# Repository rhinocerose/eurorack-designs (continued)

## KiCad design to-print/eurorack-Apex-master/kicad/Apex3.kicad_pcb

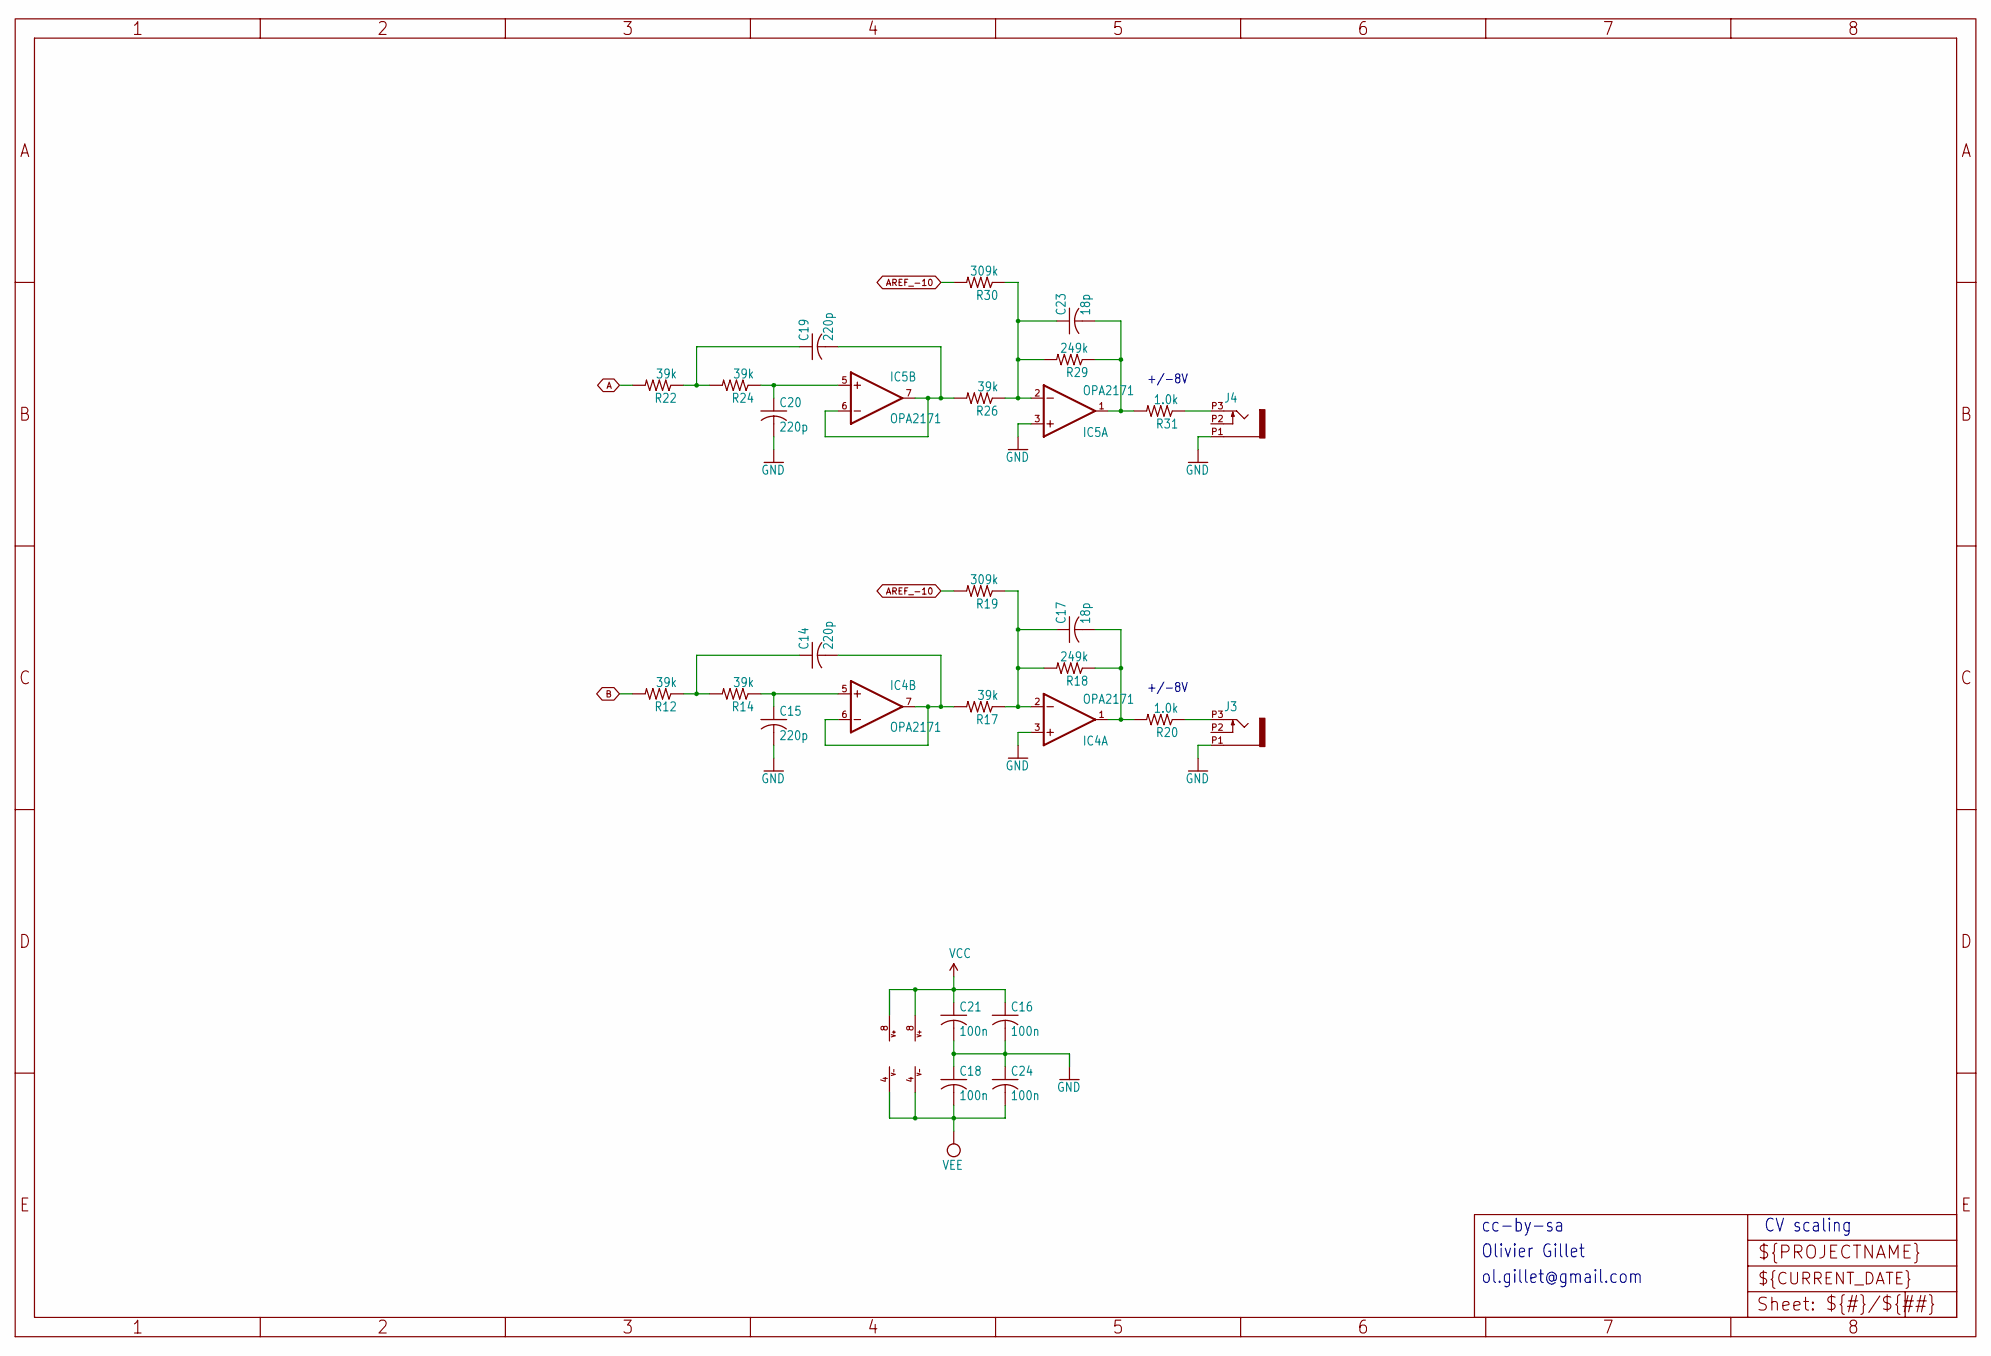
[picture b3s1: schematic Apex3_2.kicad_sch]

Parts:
C14, C15, C19, C20: 220p; C0603
C16, C18, C21, C24: 100n; C0603
C17, C23: 18p; C0603
IC4, IC5: OPA2171; SO08
J3, J4: OG-PJ301_PJ301_THONKICONN; OG-PJ301_WQP_PJ_301M6_NO_HOLE
R12, R14, R17, R22, R24, R26: 39k; R0603
R18, R29: 249k; R0603
R19, R30: 309k; R0603
R20, R31: 1.0k; R0603

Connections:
A: R22.2; also elsewhere on the board
AREF_-10: R19.2, R30.2; also elsewhere on the board
B: R12.2; also elsewhere on the board
BI_OUT: C17.2, IC4.1 (OUT), R18.1, R20.2
BI_OUT1: C23.2, IC5.1 (OUT), R29.1, R31.2
F_CV: C17.1, IC4.2 (-IN), R17.1, R18.2, R19.1
F_CV1: C23.1, IC5.2 (-IN), R26.1, R29.2, R30.1
GND: C15.2, C16.2, C18.1, C20.2, C21.2, C24.1, IC4.3 (+IN), IC5.3 (+IN), J3.P1 (1), J4.P1 (1); also elsewhere on the board
unnamed: C19.2, IC5.6 (-IN), IC5.7 (OUT), R26.2
unnamed: C20.1, IC5.5 (+IN), R24.1
unnamed: C19.1, R22.1, R24.2
unnamed: J3.P3 (3), R20.1
unnamed: J4.P3 (3), R31.1
unnamed: C14.2, IC4.6 (-IN), IC4.7 (OUT), R17.2
unnamed: C15.1, IC4.5 (+IN), R14.1
unnamed: C14.1, R12.1, R14.2
VCC: C16.1, C21.1, IC4.8 (V+), IC5.8 (V+); also elsewhere on the board
VEE: C18.2, C24.2, IC4.4 (V-), IC5.4 (V-); also elsewhere on the board

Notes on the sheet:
cc-by-sa
+/-8V
Olivier Gillet
CV scaling
ol.gillet@gmail.com

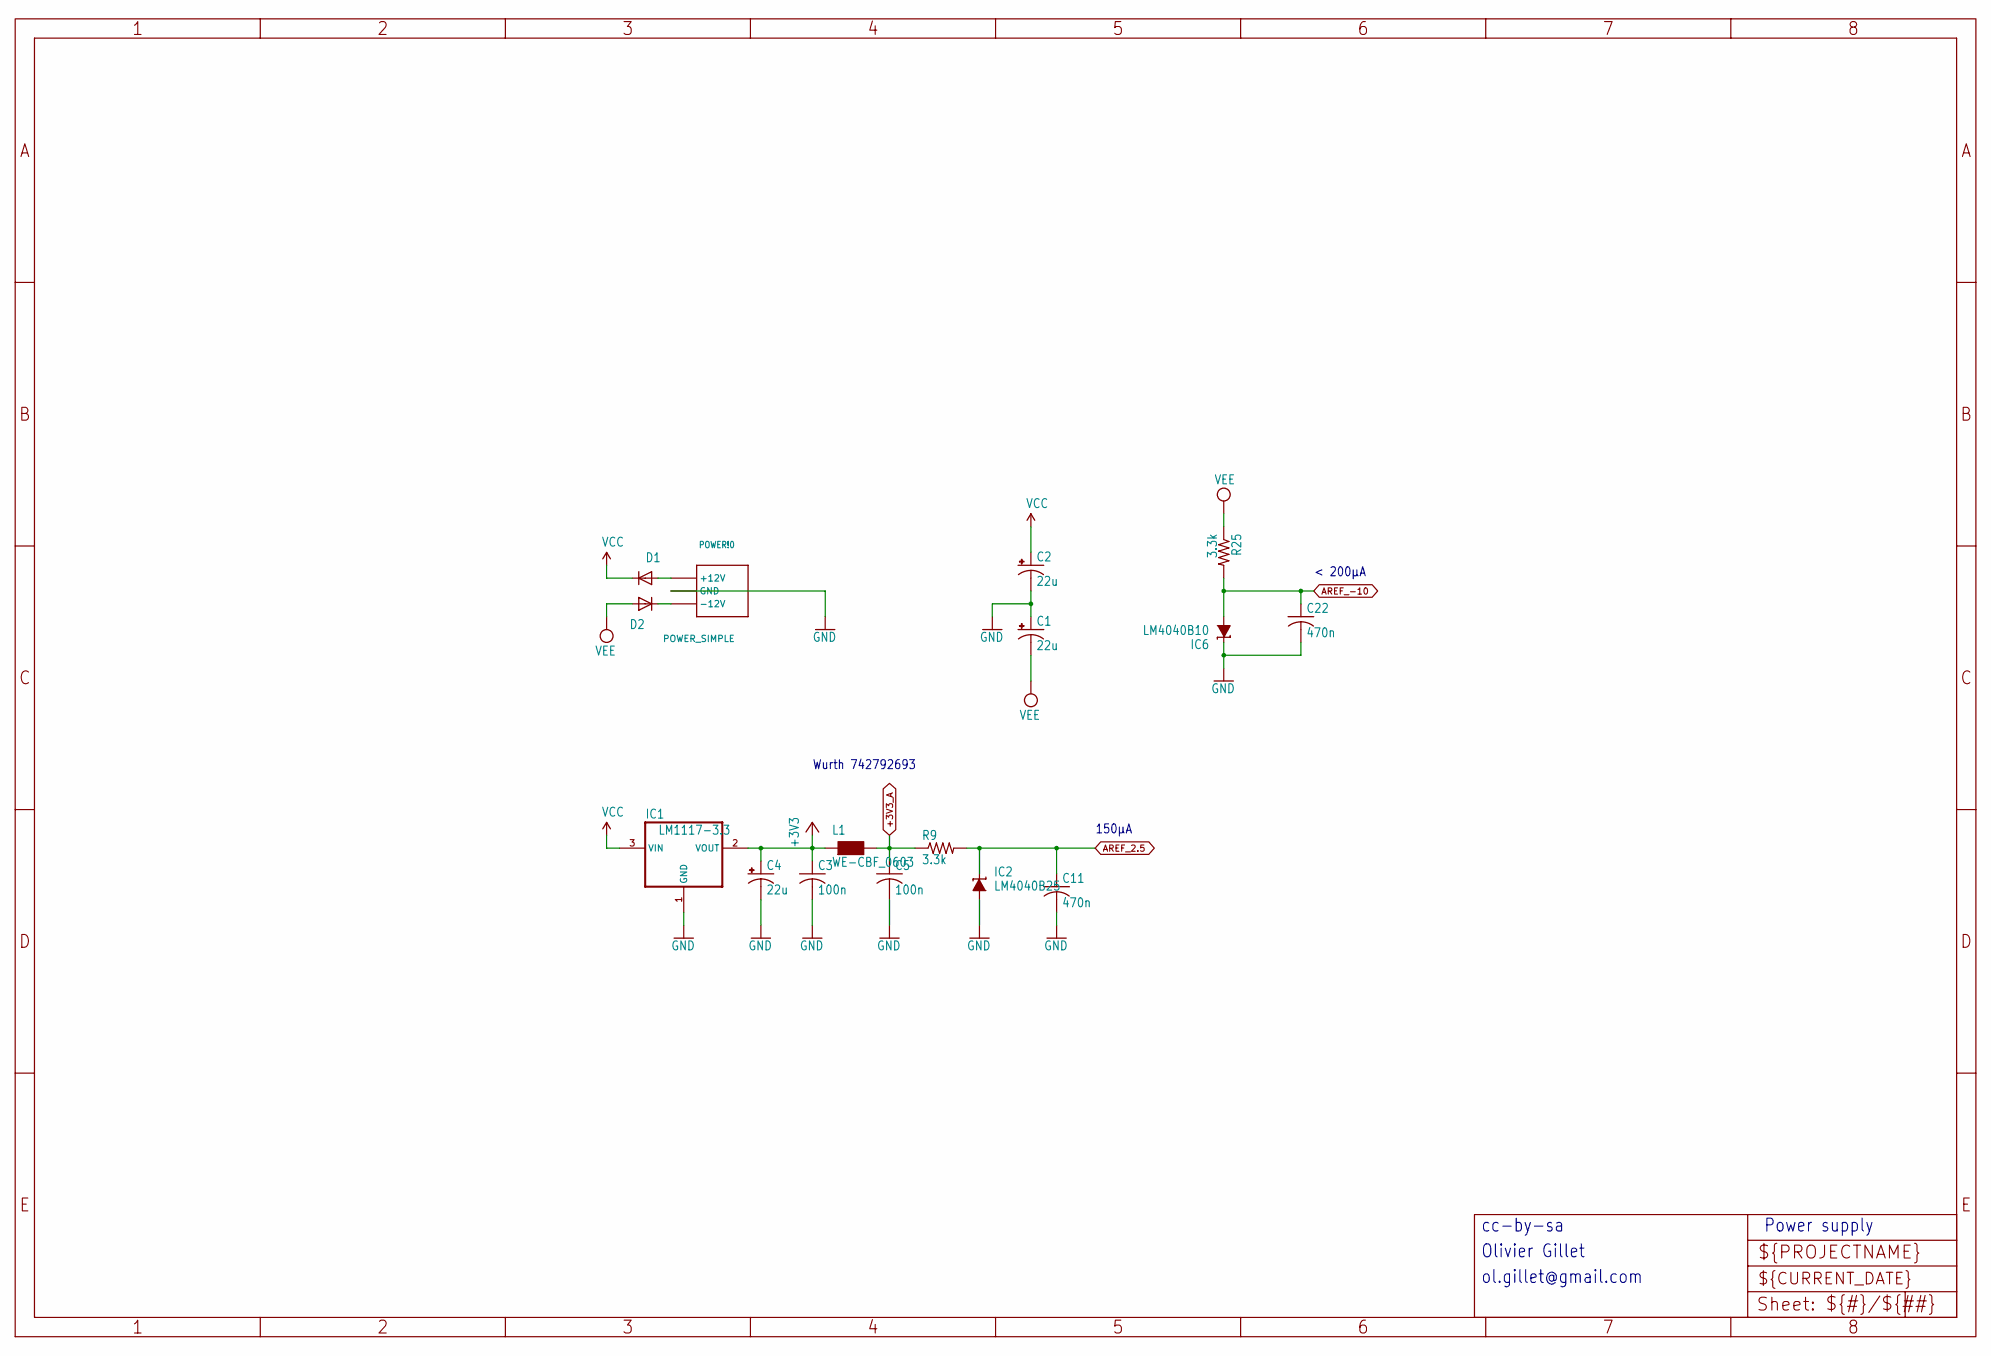
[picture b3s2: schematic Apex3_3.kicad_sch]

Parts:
C1, C2, C4: 22u; PANASONIC_C
C3, C5: 100n; C0603
C11, C22: 470n; C0603
D1, D2: 1N5819HW; SOD123
IC1: LM1117-3.3; SOT223
IC2: LM4040B25; DBZ_R-PDSO-G3
IC6: LM4040B10; DBZ_R-PDSO-G3
L1: WE-CBF_0603; 0603
POWER!0: POWER_SIMPLE; 2X05_SMT_HEADER
R9, R25: 3.3k; R0603

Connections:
+3V3: C3.1, C4.+, IC1.2 (VOUT), L1.1; also elsewhere on the board
+3V3_A: C5.1, L1.2, R9.1; also elsewhere on the board
AREF_2.5: C11.1, IC2.1 (C), R9.2; also elsewhere on the board
AREF_-10: C22.1, IC6.2 (A), R25.2; also elsewhere on the board
GND: C1.+, C2.-, C3.2, C4.-, C5.2, C11.2, C22.2, IC1.1 (GND), IC2.2 (A), IC6.1 (C), POWER!0.3 (GND), POWER!0.4 (GND), POWER!0.5 (GND), POWER!0.6 (GND), POWER!0.7 (GND), POWER!0.8 (GND); also elsewhere on the board
unnamed: D1.A, POWER!0.9 (+12V), POWER!0.10 (+12V)
unnamed: D2.C, POWER!0.1 (-12V), POWER!0.2 (-12V)
VCC: C2.+, D1.C, IC1.3 (VIN); also elsewhere on the board
VEE: C1.-, D2.A, R25.1; also elsewhere on the board

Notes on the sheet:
ol.gillet@gmail.com
Olivier Gillet
Wurth 742792693
150µA
Power supply
cc-by-sa
< 200µA

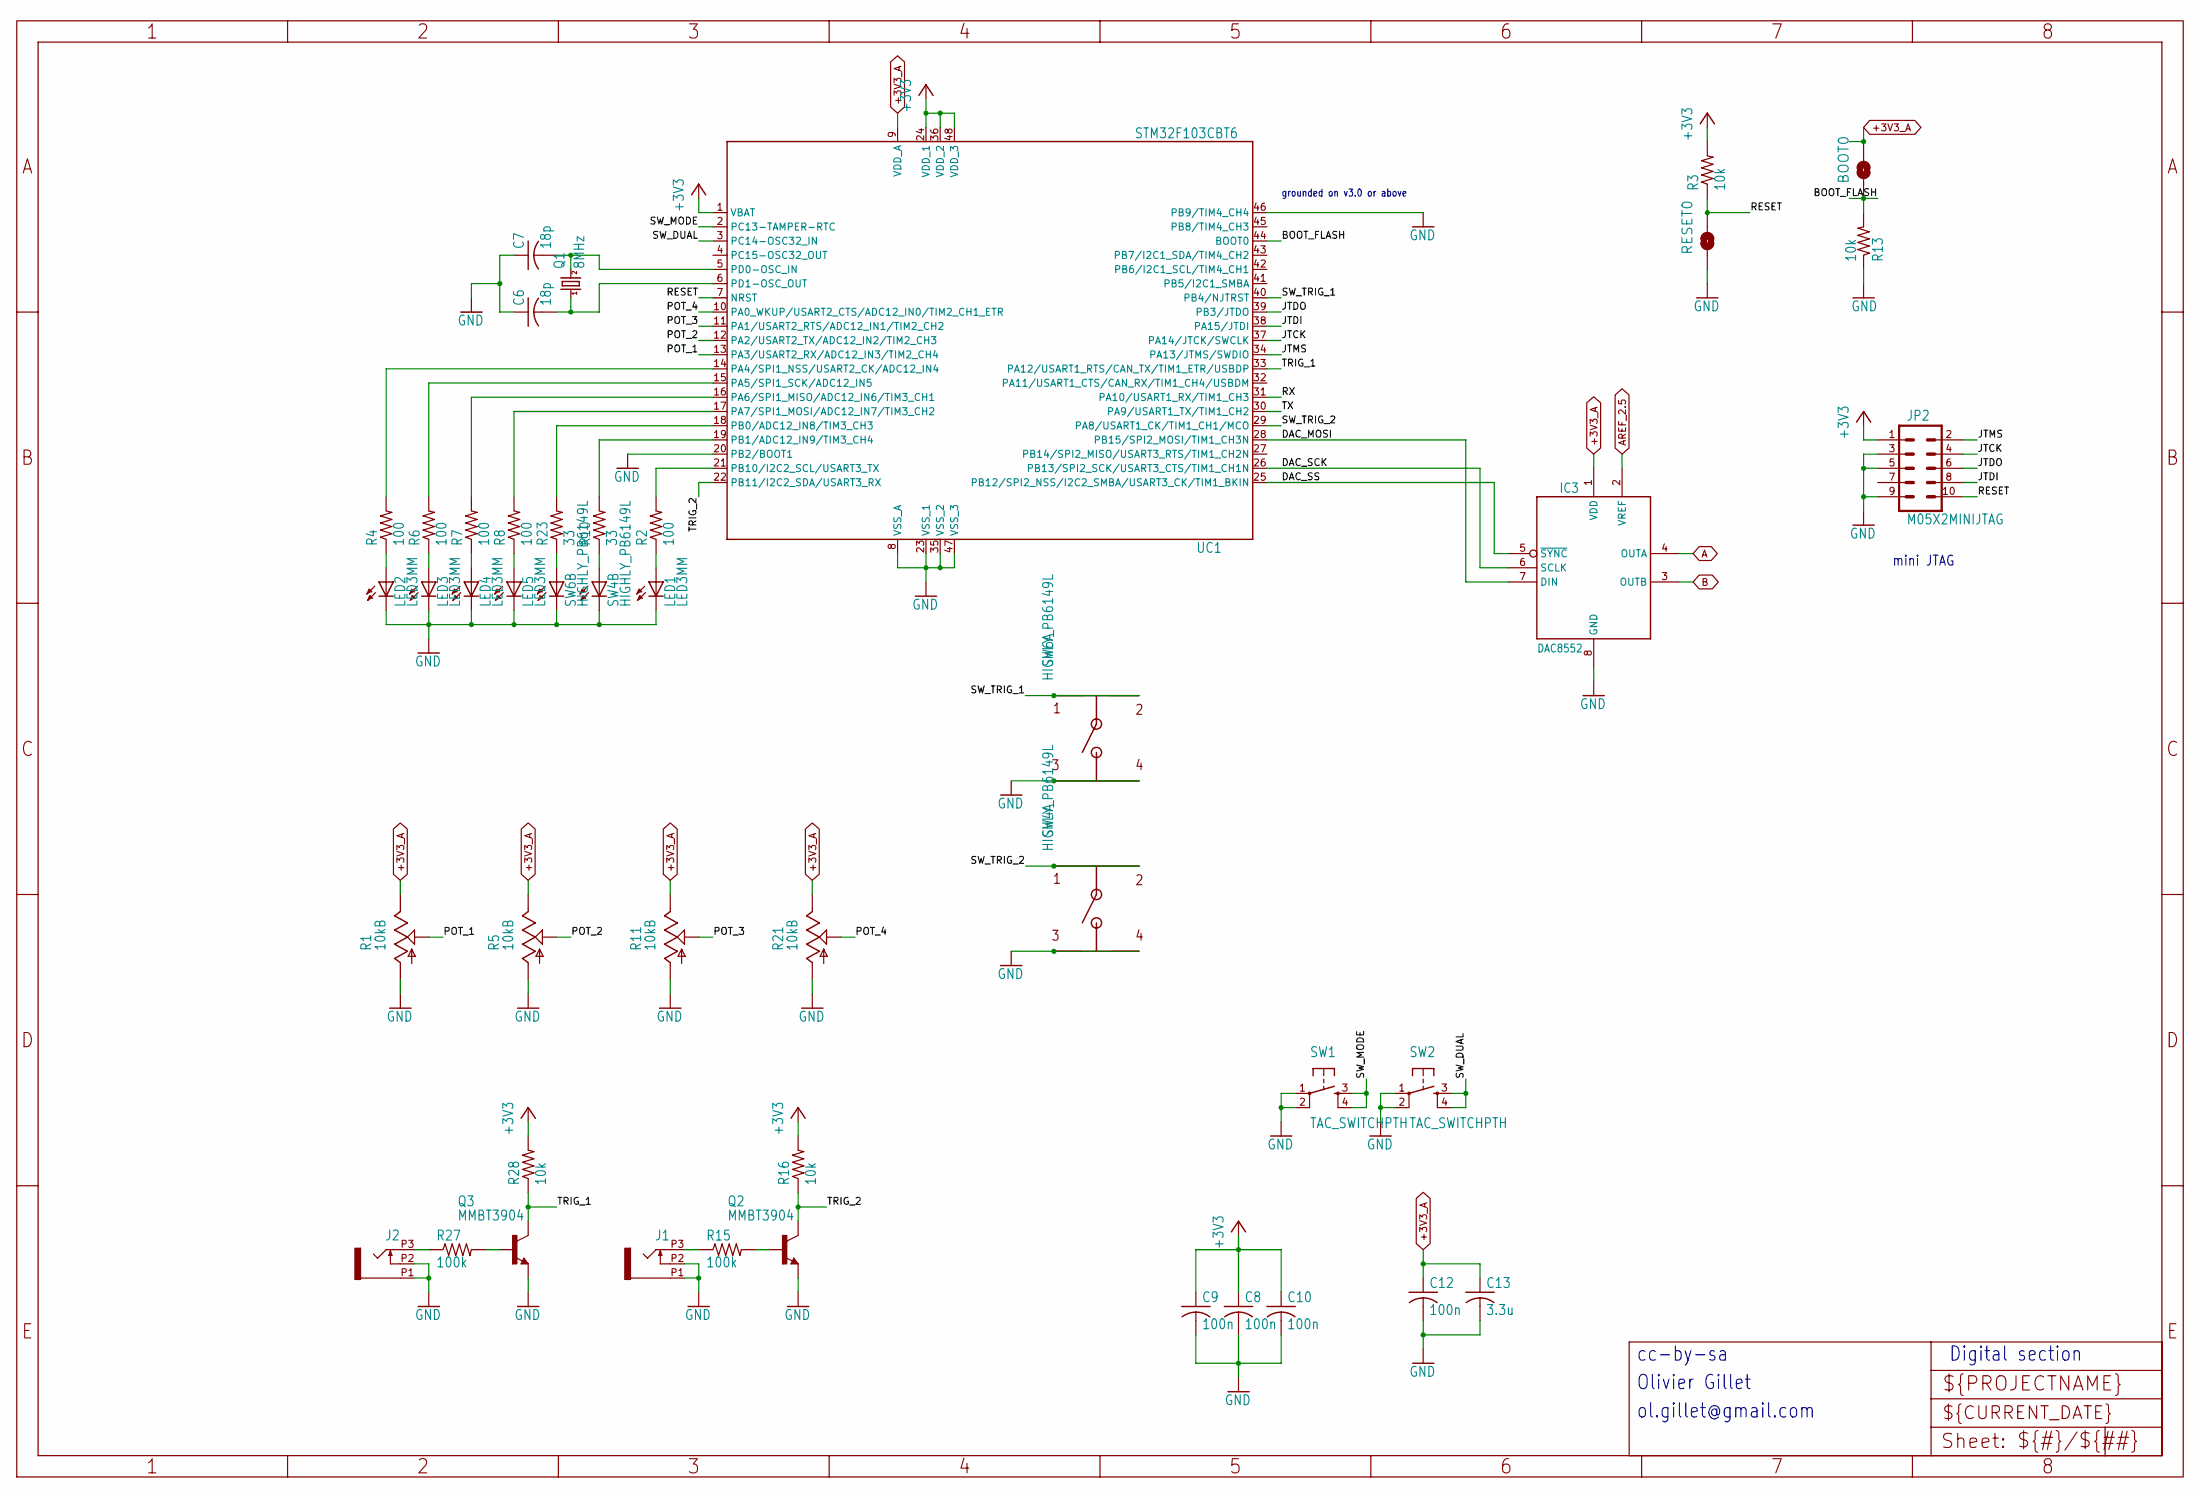
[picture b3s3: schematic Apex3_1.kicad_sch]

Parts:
BOOT0: BOOT; SMT-JUMPER_2_NO_SILK
C6, C7: 18p; C0603
C8, C9, C10, C12: 100n; C0603
C13: 3.3u; C0603
IC3: DAC8552; MSOP-8
J1, J2: OG-PJ301_PJ301_THONKICONN; OG-PJ301_WQP_PJ_301M6_NO_HOLE
JP2: M05X2MINIJTAG; 2X5-1.27
LED1, LED2, LED3, LED4, LED5: LED3MM
Q1: 8MHz; HC49UP
Q2, Q3: MMBT3904; SOT23-BEC
R1, R5, R11, R21: 10kB; POT-ALPS_ALPS_POT_VERTICAL
R2, R4, R6, R7, R8: 100; R0603
R3, R13, R16, R28: 10k; R0603
R10, R23: 33; R0603
R15, R27: 100k; R0603
RESET0: RESET; SMT-JUMPER_2_NO_SILK
SW1, SW2: TAC_SWITCHPTH; TACTILE-PTH
SW4, SW6: HIGHLY_PB6149L; HIGHLY_PB64149L
UC1: STM32F103CBT6; LQFP48

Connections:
+3V3: C8.1, C9.1, C10.1, JP2.1, R3.2, R16.2, R28.2, UC1.1 (VBAT), UC1.24 (VDD_1), UC1.36 (VDD_2), UC1.48 (VDD_3); also elsewhere on the board
+3V3_A: BOOT0.2, C12.1, C13.1, IC3.1 (VDD), R1.P$1 (E), R5.P$1 (E), R11.P$1 (E), R21.P$1 (E), UC1.9 (VDD_A); also elsewhere on the board
A: IC3.4 (OUTA); also elsewhere on the board
AREF_2.5: IC3.2 (VREF); also elsewhere on the board
B: IC3.3 (OUTB); also elsewhere on the board
BOOT_FLASH: BOOT0.1, R13.2, UC1.44 (BOOT0)
DAC_MOSI: IC3.7 (DIN), UC1.28 (PB15/SPI2_MOSI/TIM1_CH3N)
DAC_SCK: IC3.6 (SCLK), UC1.26 (PB13/SPI2_SCK/USART3_CTS/TIM1_CH1N)
DAC_SS: IC3.5 (~SYNC), UC1.25 (PB12/SPI2_NSS/I2C2_SMBA/USART3_CK/TIM1_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)
GND: C6.1, C7.1, C8.2, C9.2, C10.2, C12.2, C13.2, IC3.8 (GND), J1.P1 (1), J1.P2 (2), J2.P1 (1), J2.P2 (2), JP2.3, JP2.5, JP2.9, LED1.K (C), LED2.K (C), LED3.K (C), LED4.K (C), LED5.K (C), Q2.E, Q3.E, R1.P$3 (A), R5.P$3 (A), R11.P$3 (A), R13.1, R21.P$3 (A), RESET0.1, SW1.1, SW1.2, SW2.1, SW2.2, SW4.L2, SW4.P$3, SW4.P$4, SW6.L2, SW6.P$3, SW6.P$4, UC1.8 (VSS_A), UC1.20 (PB2/BOOT1), UC1.23 (VSS_1), UC1.35 (VSS_2), UC1.46 (PB9/TIM4_CH4), UC1.47 (VSS_3); also elsewhere on the board
JTCK: JP2.4, UC1.37 (PA14/JTCK/SWCLK)
JTDI: JP2.8, UC1.38 (PA15/JTDI)
JTDO: JP2.6, UC1.39 (PB3/JTDO)
JTMS: JP2.2, UC1.34 (PA13/JTMS/SWDIO)
unnamed: J1.P3 (3), R15.1
unnamed: R23.2, UC1.18 (PB0/ADC12_IN8/TIM3_CH3)
unnamed: LED2.A, R4.1
unnamed: LED3.A, R6.1
unnamed: LED4.A, R7.1
unnamed: LED5.A, R8.1
unnamed: C7.2, Q1.2, UC1.5 (PD0-OSC_IN)
unnamed: C6.2, Q1.1, UC1.6 (PD1-OSC_OUT)
unnamed: R10.2, UC1.19 (PB1/ADC12_IN9/TIM3_CH4)
unnamed: R4.2, UC1.14 (PA4/SPI1_NSS/USART2_CK/ADC12_IN4)
unnamed: R6.2, UC1.15 (PA5/SPI1_SCK/ADC12_IN5)
unnamed: R7.2, UC1.16 (PA6/SPI1_MISO/ADC12_IN6/TIM3_CH1)
unnamed: R8.2, UC1.17 (PA7/SPI1_MOSI/ADC12_IN7/TIM3_CH2)
unnamed: Q2.B, R15.2
unnamed: R23.1, SW6.L1
unnamed: R10.1, SW4.L1
unnamed: LED1.A, R2.1
unnamed: R2.2, UC1.21 (PB10/I2C2_SCL/USART3_TX)
unnamed: J2.P3 (3), R27.1
unnamed: Q3.B, R27.2
POT_1: R1.P$2 (S), UC1.13 (PA3/USART2_RX/ADC12_IN3/TIM2_CH4)
POT_2: R5.P$2 (S), UC1.12 (PA2/USART2_TX/ADC12_IN2/TIM2_CH3)
POT_3: R11.P$2 (S), UC1.11 (PA1/USART2_RTS/ADC12_IN1/TIM2_CH2)
POT_4: R21.P$2 (S), UC1.10 (PA0_WKUP/USART2_CTS/ADC12_IN0/TIM2_CH1_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)
RESET: JP2.10, R3.1, RESET0.2, UC1.7 (NRST)
RX: UC1.31 (PA10/USART1_RX/TIM1_CH3)
SW_DUAL: SW2.3, SW2.4, UC1.3 (PC14-OSC32_IN)
SW_MODE: SW1.3, SW1.4, UC1.2 (PC13-TAMPER-RTC)
SW_TRIG_1: SW6.P$1, SW6.P$2, UC1.40 (PB4/NJTRST)
SW_TRIG_2: SW4.P$1, SW4.P$2, UC1.29 (PA8/USART1_CK/TIM1_CH1/MCO)
TRIG_1: Q3.C, R28.1, UC1.33 (PA12/USART1_RTS/CAN_TX/TIM1_ETR/USBDP)
TRIG_2: Q2.C, R16.1, UC1.22 (PB11/I2C2_SDA/USART3_RX)
TX: UC1.30 (PA9/USART1_TX/TIM1_CH2)

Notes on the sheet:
grounded on v3.0 or above
ol.gillet@gmail.com
Digital section
mini JTAG
Olivier Gillet
cc-by-sa

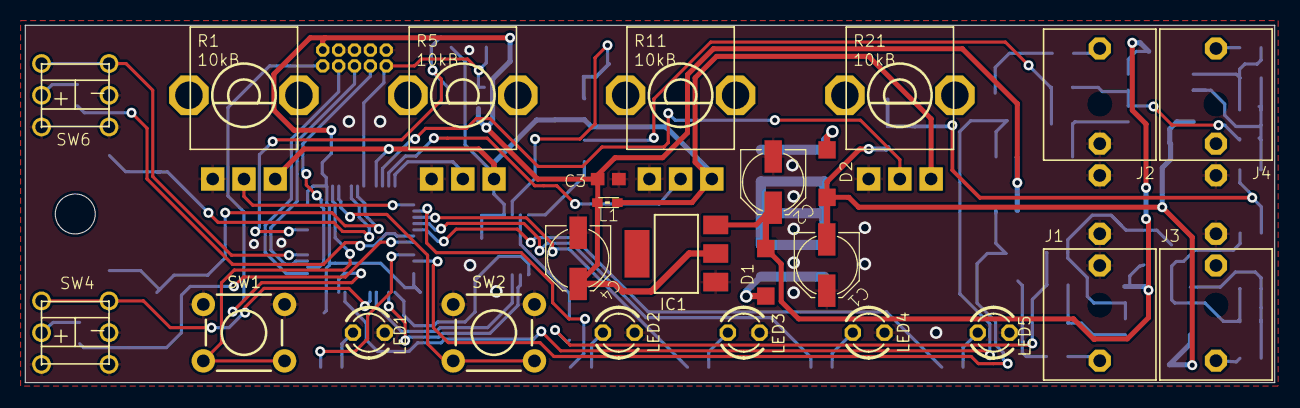
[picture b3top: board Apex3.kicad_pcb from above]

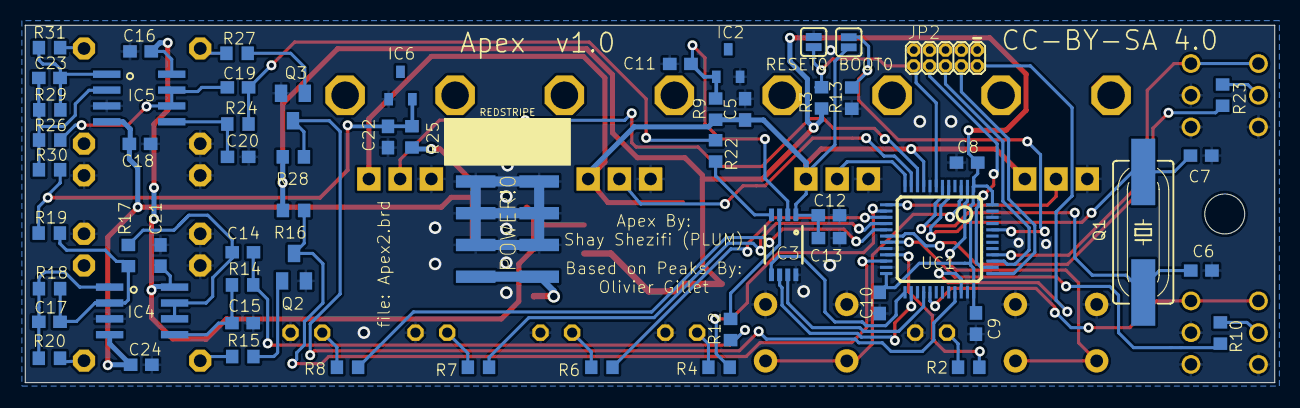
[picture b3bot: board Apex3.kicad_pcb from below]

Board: 2 copper layers, 100.0 x 28.6 mm, 86 parts (60 on the bottom side), 62 nets.

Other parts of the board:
@HOLE0: (no value)

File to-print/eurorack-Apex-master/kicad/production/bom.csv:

Designator,Footprint,Quantity,Value,LCSC Part #
@HOLE0,,1,,
BOOT0,SMT-JUMPER_2_NO_SILK_528,1,BOOT,
"C1, C2, C4",PANASONIC_C,3,22u,
"C10, C12, C16, C18, C21, C24, C3, C5, C8, C9",C0603,10,100n,
"C11, C22",C0603,2,470n,
C13,C0603,1,3.3u,
"C14, C15, C19, C20",C0603,4,220p,
"C17, C23, C6, C7",C0603,4,18p,
"D1, D2",SOD123,2,1N5819HW,
IC1,SOT223,1,LM1117-3.3,
IC2,DBZ_R-PDSO-G3,1,LM4040B25,
IC3,MSOP-8,1,DAC8552,
"IC4, IC5",SO08,2,OPA2171,
IC6,DBZ_R-PDSO-G3,1,LM4040B10,
"J1, J2, J3, J4",OG-PJ301_WQP_PJ_301M6_NO_HOLE,4,OG-PJ301_PJ301_THONKICONN,
JP2,2X5-1.27,1,M05X2MINIJTAG,
L1,0603,1,,
"LED1, LED2, LED3, LED4, LED5",LED3MM,5,,
POWER!0,2X05_SMT_HEADER,1,POWER_SIMPLE,
Q1,HC49UP,1,8MHz,
"Q2, Q3",SOT23-BEC,2,MMBT3904,
"R1, R11, R21, R5",POT-ALPS_ALPS_POT_VERTICAL,4,10kB,
"R10, R23",R0603,2,33,
"R12, R14, R17, R22, R24, R26",R0603,6,39k,
"R13, R16, R28, R3",R0603,4,10k,
"R15, R27",R0603,2,100k,
"R18, R29",R0603,2,249k,
"R19, R30",R0603,2,309k,
"R2, R4, R6, R7, R8",R0603,5,100,
"R20, R31",R0603,2,1.0k,
"R25, R9",R0603,2,3.3k,
RESET0,SMT-JUMPER_2_NO_SILK_528,1,RESET,
"SW1, SW2",TACTILE-PTH,2,,
"SW4, SW6",HIGHLY_PB64149L,2,HIGHLY_PB6149L,
UC1,LQFP48,1,STM32F103CBT6,

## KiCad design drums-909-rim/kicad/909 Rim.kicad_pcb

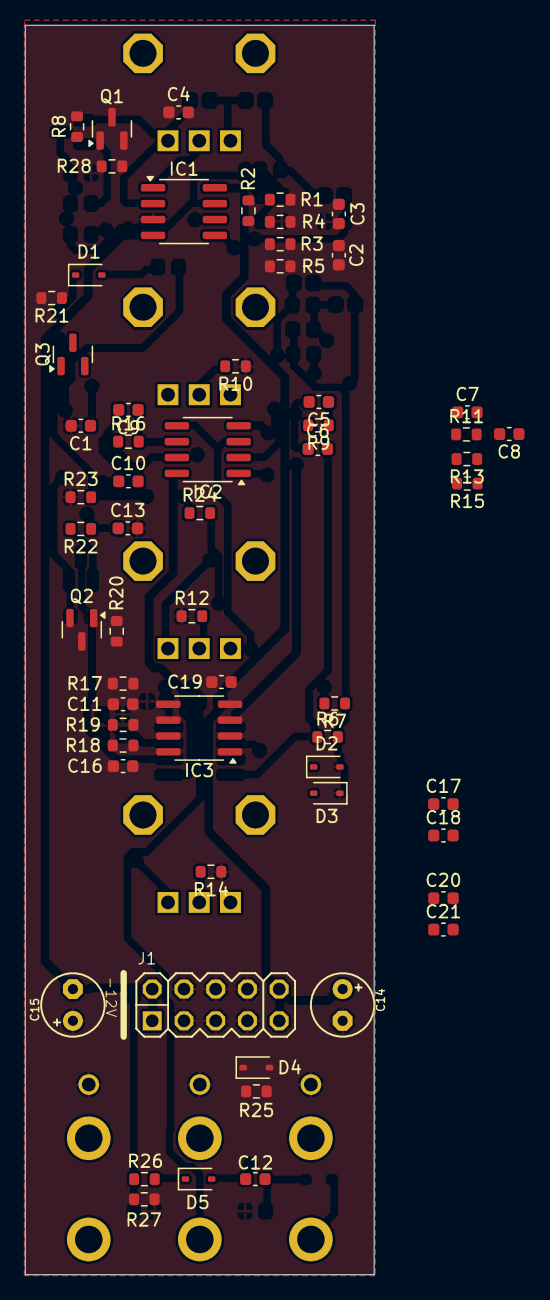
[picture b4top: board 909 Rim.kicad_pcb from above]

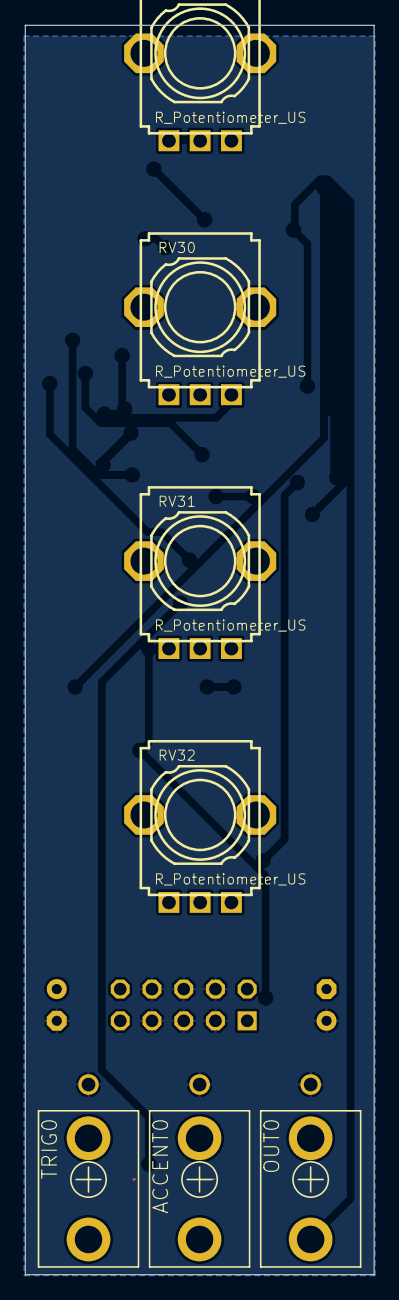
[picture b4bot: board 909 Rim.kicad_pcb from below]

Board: 2 copper layers, 27.9 x 100.0 mm, 68 parts (7 on the bottom side), 40 nets.

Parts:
ACCENT0: Accent; KOBICONN_PJM301DM_JACK_1879502
C1, C2, C3, C5, C6: 10nf; C_0603_1608Metric
C4: 220pf; C_0603_1608Metric
C7, C8: 27nf; C_0603_1608Metric
C9, C10: 4.7nf; C_0603_1608Metric
C11: 100pf; C_0603_1608Metric
C12: 15nf; C_0603_1608Metric
C13: 47nf; C_0603_1608Metric
C14, C15: 10uF; E2,5-5_1879502
C16, C17, C18, C19, C20, C21: 100nf; C_0603_1608Metric
D1, D2, D3, D4, D5: 1N4148; D_SOD-323
IC1, IC2, IC3: TL072; SOIC-8_3.9x4.9mm_P1.27mm
J1: HEADER-EUROPWR_2X05-OPEN; 2X05_EUROPWR_OPEN_1879502
OUT0: Accent; KOBICONN_PJM301DM_JACK_1879502
Q1, Q3: BC849; SOT-23
Q2: BC859; SOT-23
R1: 1K; R_0603_1608Metric
R2, R4: 4.7K; R_0603_1608Metric
R3: 22K; R_0603_1608Metric
R5: 220K; R_0603_1608Metric
R6, R7, R13: 12K; R_0603_1608Metric
R8: 680R; R_0603_1608Metric
R9, R16: 470k; R_0603_1608Metric
R10, R12, R14: 100R; R_0603_1608Metric
R11: 330K; R_0603_1608Metric
R15: 3.3k; R_0603_1608Metric
R17, R25: 100k; R_0603_1608Metric
R18, R23: 10k; R_0603_1608Metric
R19: 4.7k; R_0603_1608Metric
R20, R28: 1M; R_0603_1608Metric
R21: 47k; R_0603_1608Metric
R22: 2.7k; R_0603_1608Metric
R24, R26, R27: 22k; R_0603_1608Metric
RV29, RV30, RV31, RV32: R_Potentiometer_US; 9MM_PLS_1879502
TRIG0: KOBICONN_PJM301DM_JACK_1879502

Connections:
+12V: C14.+, J1.9, J1.10
-12V: C15.-, J1.1, J1.2
GND: ACCENT0.P$3, C1.2, C11.2, C13.2, C14.-, C15.+, C16.2, C17.2, C18.2, C19.1, C20.1, C21.1, D2.2 (A), D3.1 (K), IC1.3 (+), J1.3, J1.4, J1.5, J1.6, J1.7, J1.8, OUT0.P$3, Q3.2 (E), R4.1, R5.1, R8.1, R10.1, R12.1, R14.1, R19.2, R23.1, R25.2, R27.2, TRIG0.P$3
unnamed: ACCENT0.P$1, C11.1, IC3.5 (+), R17.1
unnamed: C2.1, C3.2, R3.1
unnamed: C5.2, C6.1, RV30.3
unnamed: C7.2, C8.1, RV31.3
unnamed: C8.2, IC2.1, R11.2, R13.1
unnamed: C9.2, C10.1, RV32.3
unnamed: C13.1, R22.1, R28.1
unnamed: D1.2 (A), R21.1
unnamed: D1.1 (K), Q3.3 (C)
unnamed: D2.1 (K), D3.2 (A), R6.2, R7.1, R13.2, R15.2
unnamed: C12.1, D4.1 (K), R25.1
unnamed: C12.2, D5.2 (A), R24.2
unnamed: D5.1 (K), R26.1
unnamed: C4.1, IC1.2 (-), Q1.2 (E), RV29.3
unnamed: C3.1, C4.2, IC1.1, RV29.1, RV29.2
unnamed: C2.2, IC1.5 (+), R5.2
unnamed: IC1.6 (-), R2.1, R3.2, R4.2
unnamed: IC1.7, R1.1, R2.2
unnamed: IC2.3 (+), IC2.5 (+), IC3.3 (+), R26.2, R27.1
unnamed: C7.1, IC2.2 (-)
unnamed: C9.1, IC2.6 (-), R16.2
unnamed: C10.2, IC2.7, R15.1, R16.1
unnamed: C5.1, IC3.2 (-), R9.1
unnamed: C6.2, IC3.1, R6.1, R9.2
unnamed: IC3.6 (-), R18.2, R19.1
unnamed: IC3.7, Q2.3 (C), R18.1, R20.2
unnamed: C1.1, R1.2
unnamed: Q1.1 (B), R28.2
unnamed: Q1.3 (C), R7.2, R8.2
unnamed: Q2.1 (B), R20.1, R21.2
unnamed: Q2.2 (E), R22.2
unnamed: Q3.1 (B), R23.2, R24.1
unnamed: R10.2, RV30.2
unnamed: R12.2, RV31.2
unnamed: R14.2, RV32.2
POWER+12V: C16.1, C17.1, C18.1, IC1.8 (V+), IC2.8 (V+), IC3.8 (V+), R17.2
POWER-12V: C19.2, C20.2, C21.2, IC1.4 (V-), IC2.4 (V-), IC3.4 (V-)

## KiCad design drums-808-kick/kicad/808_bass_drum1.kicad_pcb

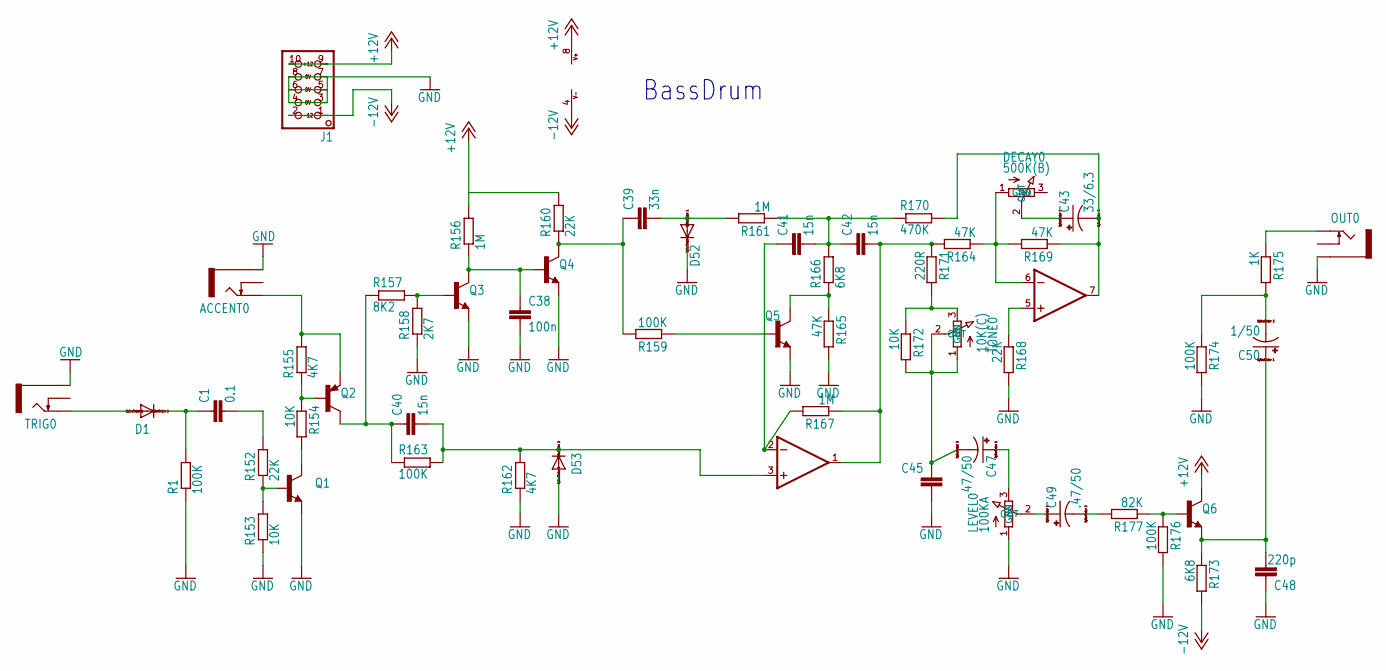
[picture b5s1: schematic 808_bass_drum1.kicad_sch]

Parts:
ACCENT0: JACK_THONKICONNNEW; WQP-PJ301M-12_JACK
C1: 0.1; C0603
C38, C45: 100n; C0603
C39: 33n; C0603
C40, C41, C42: 15n; C0603
C43: 33/6.3; E2,5-5
C47, C49: .47/50; E2,5-5
C48: 220p; C0603
C50: 1/50; E2,5-5
D1, D52, D53: 1N4148; SOD323W_INFINEON
DECAY0: 500K(B); 9MM_PLS
IC1: OPAMP-TL072D; SO08
J1: HEADER-EUROPWR_2X05-OPEN; 2X05_EUROPWR_OPEN
LEVEL0: 100KA; 9MM_PLS
OUT0: JACK_THONKICONNNEW; WQP-PJ301M-12_JACK
Q1, Q3, Q4, Q5, Q6: bc546; SOT23-BEC
Q2: bc556; SOT23-BEC
R1, R159, R163, R174, R176: 100K; R0603
R152, R160, R168: 22K; R0603
R153, R154, R172: 10K; R0603
R155, R162: 4K7; R0603
R156, R161, R167: 1M; R0603
R157: 8K2; R0603
R158: 2K7; R0603
R164, R165, R169: 47K; R0603
R166, R173: 6K8; R0603
R170: 470K; R0603
R171: 220R; R0603
R175: 1K; R0603
R177: 82K; R0603
TONE0: 10K(C); 9MM_PLS
TRIG0: JACK_THONKICONNNEW; WQP-PJ301M-12_JACK

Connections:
+12V: IC1.8 (V+), J1.9, J1.10, Q6.C, R156.2, R160.2
-12V: IC1.4 (V-), J1.1, J1.2, R173.2
C49: C49.-, R177.2
GND: ACCENT0.P$3_SLEEVE (SLEEVE), C38.2, C45.2, C48.1, D52.C, D53.A, J1.3, J1.4, J1.5, J1.6, J1.7, J1.8, LEVEL0.1 (GND), OUT0.P$3_SLEEVE (SLEEVE), Q1.E, Q3.E, Q4.E, Q5.E, R1.1, R153.1, R158.1, R162.1, R165.2, R168.2, R174.2, R176.2, TRIG0.P$3_SLEEVE (SLEEVE)
unnamed: DECAY0.1 (GND), IC1.6 (-IN), R164.1, R169.2
unnamed: IC1.5 (+IN), R168.1
unnamed: OUT0.P$1_TIP (TIP), R175.1
unnamed: D1.A, TRIG0.P$1_TIP (TIP)
unnamed: C1.1, D1.C, R1.2
unnamed: C1.2, R152.2
unnamed: C38.1, Q3.C, Q4.B, R156.1
unnamed: Q2.B, R154.1, R155.1
unnamed: Q5.C, R165.1, R166.1
unnamed: Q3.B, R157.2, R158.2
unnamed: Q1.C, R154.2
unnamed: C39.1, Q4.C, R159.2, R160.1
unnamed: C40.1, Q2.C, R157.1, R163.1
unnamed: C40.2, D53.C, IC1.3 (+IN), R162.2, R163.2
unnamed: Q5.B, R159.1
unnamed: C41.2, C42.1, R161.1, R166.2, R170.1
unnamed: C41.1, IC1.2 (-IN), R167.2
unnamed: C42.2, IC1.1 (OUT), R164.2, R167.1, R171.1
unnamed: C45.1, C47.-, R172.2, TONE0.1 (GND), TONE0.2 (OUT)
unnamed: R171.2, R172.1, TONE0.3 (IN)
unnamed: C43.-, IC1.7 (OUT), R169.1, R170.2
unnamed: Q6.B, R176.1, R177.1
unnamed: C48.2, C50.+, Q6.E, R173.1
unnamed: C50.-, R174.1, R175.2
unnamed: C47.+, LEVEL0.3 (IN)
unnamed: C49.+, LEVEL0.2 (OUT)
unnamed: C43.+, DECAY0.2 (OUT)
unnamed: Q1.B, R152.1, R153.2
unnamed: C39.2, D52.A, R161.2
TRIG: ACCENT0.P$1_TIP (TIP), Q2.E, R155.2

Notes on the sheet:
BassDrum

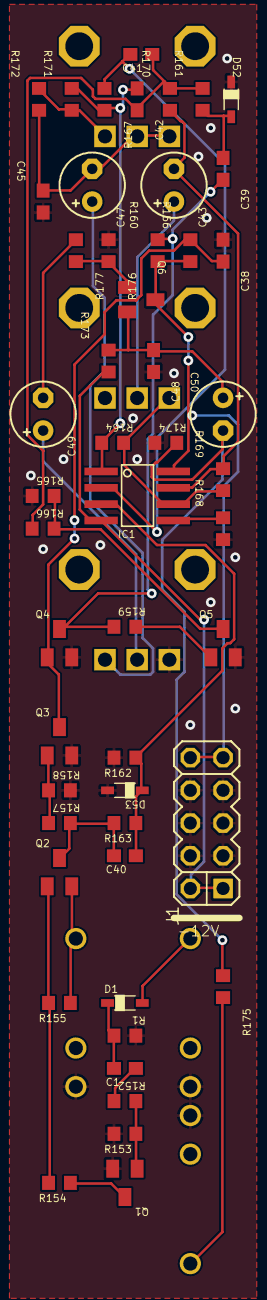
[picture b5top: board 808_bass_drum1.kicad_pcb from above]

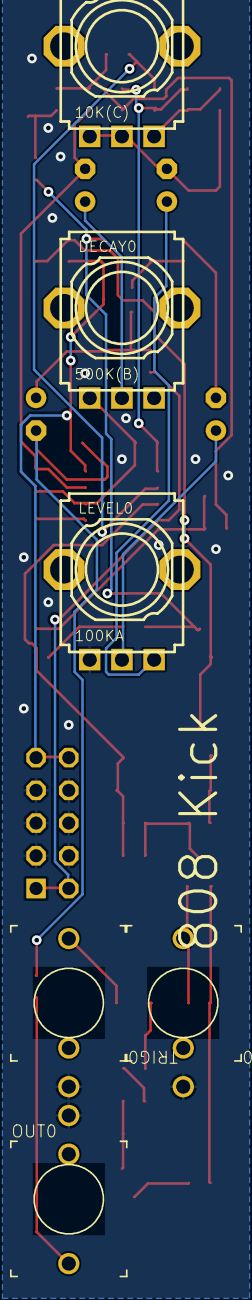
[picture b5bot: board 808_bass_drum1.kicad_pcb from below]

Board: 2 copper layers, 56 parts (6 on the bottom side), 34 nets.
